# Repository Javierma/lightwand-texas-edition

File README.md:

# Lightwand Texas Edition v 2.0

Copyright (C) May 2018, Javier Martínez Arrieta

The LightWand Texas Edition controller is released under an Attributtion-ShareAlike 4.0 International (CC BY-SA 4.0). Therefore, anyone is free to:

-Share - copy and redistribute the material in any medium or format

-Adapt - remix, transform, and build upon the material for any purpose, even commercially.

This is the Lightwand Texas Edition project, a light painting project that makes use of a TM4C123 (TIVA) board as a controller in order to read the image information and transmit it to the LED strip according to the settings.

The following folders contain all the necessary things:
	
-CCS project: Contains the software code to be uploaded to the board

-Eagle project: Contains the hardware design

-FreeCAD design: Contains the 3D design of the box to cover the hardware

-Sketchup design: Contains the 3D design of the hardware

-Lightwand Texas Edition English Guide: The manual to be used to know about the different HW parts, soldering steps, creating PNM images and how to navigate through the different menus 

In order to know how to import the project in Code Composer Studio, configure the project settings and configure interrupts, go to the [wiki page](https://github.com/Javierma/lightwand-texas-edition/wiki)

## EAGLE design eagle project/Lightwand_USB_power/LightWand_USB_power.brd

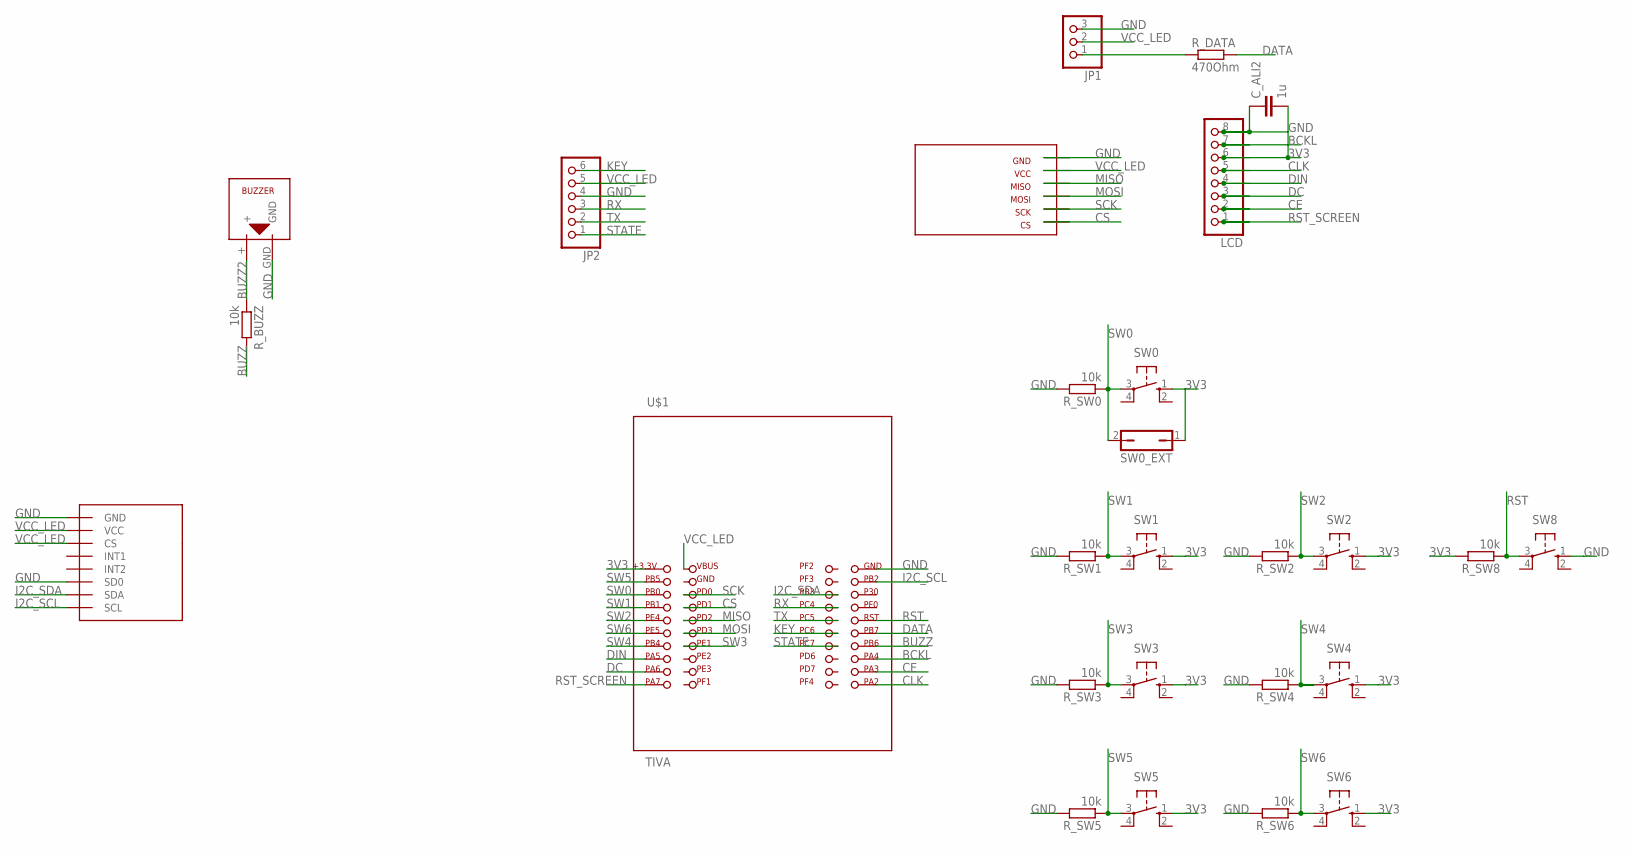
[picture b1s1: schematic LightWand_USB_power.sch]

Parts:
C_ALI2: 1u; C1206
JP1: PINHD-1X3; 1X03
JP2: PINHD-1X6; 1X06
LCD: PINHD-1X8; 1X08
R_BUZZ: 10k; R1206
R_DATA: 470Ohm; R1206
R_SW0, R_SW1, R_SW2, R_SW3, R_SW4, R_SW5, R_SW6, R_SW8: 10k; R1206
SW0, SW1, SW2, SW3, SW4, SW5, SW6, SW8: 10-XX; B3F-10XX
SW0_EXT: JP1Q; JP1
U$1: TIVA; TIVACSERIES
U$2: ADXL345
U$3: MURATA_BUZZER
U$4: SD_READER_CATALEX

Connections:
3V3: C_ALI2.2, LCD.6, R_SW8.2, SW0.1 (S), SW0_EXT.1, SW1.1 (S), SW2.1 (S), SW3.1 (S), SW4.1 (S), SW5.1 (S), SW6.1 (S), U$1.+3.3V (3.3V)
BCKL: LCD.7, U$1.PA4
BUZZ: R_BUZZ.2, U$1.PB6
BUZZ2: R_BUZZ.1, U$3.+
CE: LCD.2, U$1.PA3
CLK: LCD.5, U$1.PA2
CS: U$1.PD1, U$4.CS
DATA: R_DATA.2, U$1.PB7
DC: LCD.3, U$1.PA6
DIN: LCD.4, U$1.PA5
GND: C_ALI2.1, JP1.3, JP2.4, LCD.8, R_SW0.2, R_SW1.2, R_SW2.2, R_SW3.2, R_SW4.2, R_SW5.2, R_SW6.2, SW8.1 (S), U$1.GND1 (GND2), U$2.P$1 (GND), U$2.P$6 (SD0), U$3.GND, U$4.GND
I2C_SCL: U$1.PB2, U$2.P$7 (SCL)
I2C_SDA: U$1.PB3, U$2.P$8 (SDA)
KEY: JP2.6, U$1.PC6
MISO: U$1.PD2, U$4.MISO
MOSI: U$1.PD3, U$4.MOSI
unnamed: JP1.1, R_DATA.1
RST: R_SW8.1, SW8.3, U$1.RST
RST_SCREEN: LCD.1, U$1.PA7
RX: JP2.3, U$1.PC4
SCK: U$1.PD0, U$4.SCK
STATE: JP2.1, U$1.PC7
SW0: R_SW0.1, SW0.3, SW0_EXT.2, U$1.PB0
SW1: R_SW1.1, SW1.3, U$1.PB1
SW2: R_SW2.1, SW2.3, U$1.PE4
SW3: R_SW3.1, SW3.3, U$1.PE1
SW4: R_SW4.1, SW4.3, U$1.PB4
SW5: R_SW5.1, SW5.3, U$1.PB5
SW6: R_SW6.1, SW6.3, U$1.PE5
TX: JP2.2, U$1.PC5
VCC_LED: JP1.2, JP2.5, U$1.VBUS, U$2.P$2 (VCC), U$2.P$3 (CS), U$4.VCC

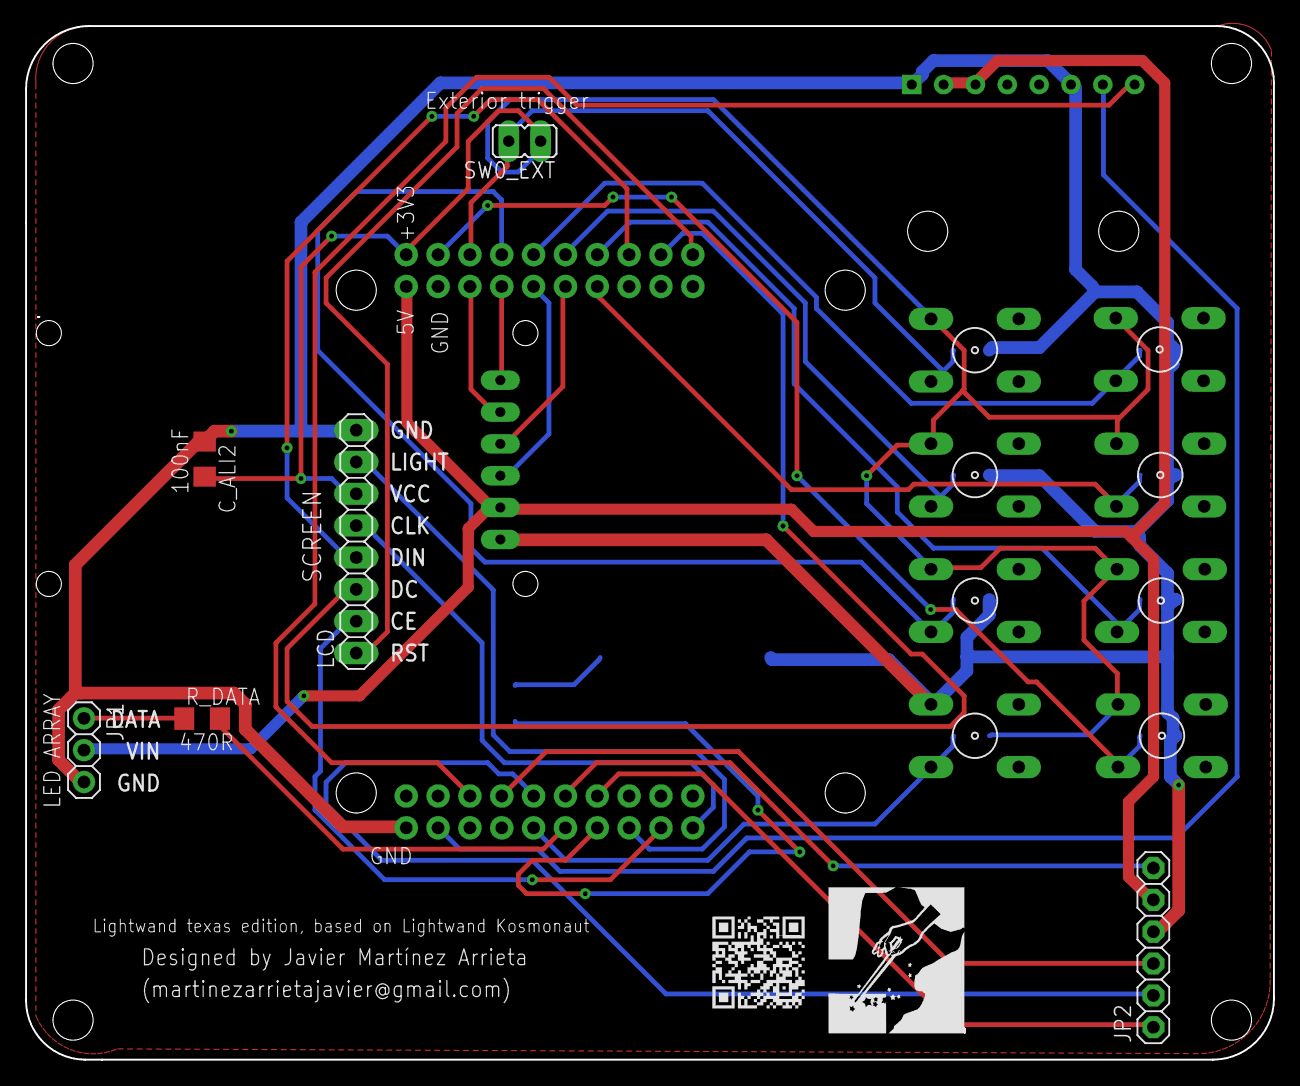
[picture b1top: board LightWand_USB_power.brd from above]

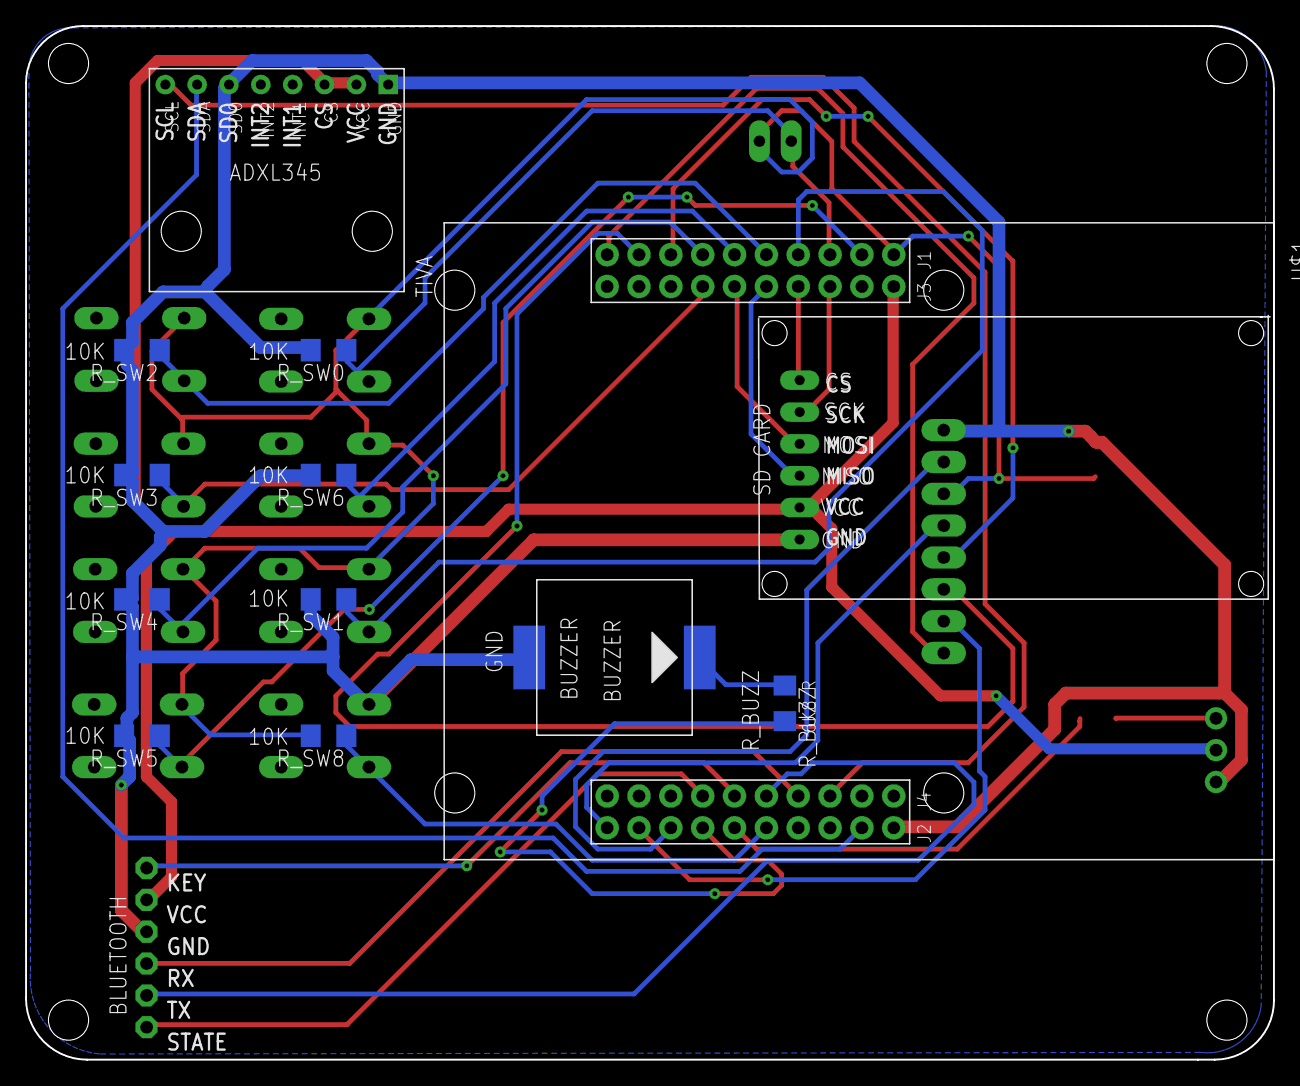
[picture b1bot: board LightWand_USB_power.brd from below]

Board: 2 copper layers, 99.5 x 82.4 mm, 27 parts (13 on the bottom side), 31 nets.

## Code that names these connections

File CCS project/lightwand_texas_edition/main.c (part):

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				{
					switch(portB_data)
					{
						case 0x01: //PB0 (Change backlight status)
						{

						break;
						}
						case 0x02: //PB1 (Select element at current position)
						{
							if(current_position==2)
							{
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				{
					switch(portE_data)
					{
						case 0x02: // PE1 (down)
						{
							if(current_position==2)
							{
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							}
							break;
						}
						case 0x20: // PE5 (up)
						{
							if(current_position==3)
							{
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    volatile unsigned long delay;
    SYSCTL_RCGC2_R |= 0x00000012;           //  activate clock for Ports B and E
    delay = SYSCTL_RCGC2_R;                 //  allow time for clock to stabilize
    GPIO_PORTB_DIR_R &= ~0x33;             // make PB0,1,4 and 5 in
    GPIO_PORTB_AFSEL_R &= ~0x33;           // disable alt funct on PA2,3,5
    GPIO_PORTB_DEN_R |= 0x33;             // enable digital I/O on PB0,1,4 and 5

    GPIO_PORTB_PCTL_R &= ~0x00FF00FF;    //Configure PB0, 1, 4 and 5 as GPIO
    GPIO_PORTB_AMSEL_R &= ~0x33;           // disable alt funct on PB0,1,4 and 5
    GPIO_PORTB_IS_R &= ~0x33;            //PB0,1,4 and 5 are edge sensitive
    GPIO_PORTB_IBE_R &= ~0x33;            //Disable both edges for PB0,1,4 and 5
    //GPIO_PORTB_IEV_R &= ~0x33;            //Detect falling edge in PB0,1,4 and 5
    GPIO_PORTB_IEV_R |= 0x33;            //Detect rising edge in PB0,1,4 and 5
    GPIO_PORTB_ICR_R = 0x33;              // ack, clear interrupt flags for PB0,1,4 and 5
    GPIO_PORTB_IM_R |= 0x33;              // arm interrupt on PB0,1,4 and 5
    NVIC_PRI0_R = (NVIC_PRI0_R&0xFFFF1FFF)|0x0000E000;         //Set priority bits for port B
    NVIC_EN0_R |= 0x00000002;      // (h) enable interrupt 1 in NVIC (seen in IRQ). Interrupt one is bit 1


    GPIO_PORTE_DIR_R &= ~0x32;             // make PE1,4 and 5 in
    GPIO_PORTE_AFSEL_R &= ~0x32;           // disable alt funct on PE1,4 and 5
    GPIO_PORTE_DEN_R |= 0x32;             // enable digital I/O on PE1,4 and 5


    GPIO_PORTE_PCTL_R &= ~0x00FF00F0;    //Configure PE1,4 and 5 as GPIO
    GPIO_PORTE_AMSEL_R &= ~0x32;           // disable alt funct on PE1, 4 and 5
    GPIO_PORTE_IS_R &= ~0x32;            //PE1, 4 and 5 are edge sensitive
    GPIO_PORTE_IBE_R &= ~0x32;            //Disable both edges for PE1, 4 and 5
    //GPIO_PORTE_IEV_R &= ~0x32;            //Detect falling edge in PE1, 4 and 5
    GPIO_PORTE_IEV_R |= 0x32;            //Detect rising edge in PE1, 4 and 5
    GPIO_PORTE_ICR_R = 0x32;              // ack, clear interrupt flags for PE1, 4 and 5
    GPIO_PORTE_IM_R |= 0x32;              // arm interrupt on PE1, PE4 and PE5
    NVIC_PRI1_R = (NVIC_PRI1_R&0xFFFFFF1F)|0x000000E0;         //Set priority bits for port E
    NVIC_EN0_R |= 0x00000010;      // (h) enable interrupt 1 in NVIC (seen in IRQ). Interrupt one is bit 4

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    int led_position=0;
    char c,c2,go_back=0,just_came=0;
    //Check which pin caused the interrupt
    //Backlight pin (PB0)
    if(GPIO_PORTB_RIS_R&0x01)
    {
        GPIO_PORTB_ICR_R |= 0x01; // ack, clear interrupt flag0
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    }
    else
    {
        //Minus/decrease pin (PB4)
        if(GPIO_PORTB_RIS_R&0x10)
        {
            GPIO_PORTB_ICR_R |= 0x10; // ack, clear interrupt flag4
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        }
        else
        {
            //Select pin (PB1)
            if(GPIO_PORTB_RIS_R&0x02)
            {
                GPIO_PORTB_ICR_R |= 0x02; // ack, clear interrupt flag1
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            }
            else
            {
                //Start pin (PB5)
                if(GPIO_PORTB_RIS_R&0x20)
                {
                    GPIO_PORTB_ICR_R |= 0x20; // ack, clear interrupt flag5
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    int led_position=0;
    char c,c2,go_back=0,just_came=0,lights=LIGHTS_OFF;
    //check which pin caused the interrupt
    //Move down pin (PE1)
    if(GPIO_PORTE_RIS_R&0x02)
    {
        GPIO_PORTE_ICR_R |= 0x02; // ack, clear interrupt flag1
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    }
    else
    {
        //More/Increase pin (PE4)
        if(GPIO_PORTE_RIS_R&0x10)
        {
            GPIO_PORTE_ICR_R |= 0x10; // ack, clear interrupt flag4
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        }
        else
        {
            //Move up pin (PE5)
            if(GPIO_PORTE_RIS_R&0x20)
            {
                GPIO_PORTE_ICR_R |= 0x20; // ack, clear interrupt flag5
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	//Port B has already been initialized, so clock does not have to be set again
	SYSCTL_RCGCI2C_R |=SYSCTL_RCGCI2C_R0; //Enable clock for the I2C module
	delay=SYSCTL_RCGCI2C_R;
	GPIO_PORTB_AFSEL_R |= 0x0C;           // disable alt funct on PB2 and 3
    // configure PB2 and 3 I2C
	GPIO_PORTB_PCTL_R = (GPIO_PORTB_PCTL_R&0xFFFF00FF)+0x00003300;
    // configure PA6,7 as GPIO
	GPIO_PORTB_PCTL_R = (GPIO_PORTB_PCTL_R&0xFF00FF0F)+0x00000000;
	GPIO_PORTB_DEN_R |= 0x0C;   // enable digital I/O on PB2 and 3
	GPIO_PORTB_ODR_R |=0x08;	// enable SDA for open drain operation
	I2C0_MCR_R |=I2C_MCR_MFE;	//Initialization of I2C master
	I2C0_MTPR_R |=0x00000007;	//Sets I2C clock speed to 100Kbps with 16MHz oscillator
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	SYSCTL_RCGCTIMER_R |= 0x01;      // activate timer0
	SYSCTL_RCGC2_R |= 0x00000002;   //  activate clock for Port B
	delay = SYSCTL_RCGC2_R;
	GPIO_PORTB_DIR_R |= 0x40;             // make PB6 out
	GPIO_PORTB_AFSEL_R |= 0x40;           // enable alt funct on PB6
	GPIO_PORTB_AMSEL_R &= ~0x40;          // disable analog functionality on PB6
	GPIO_PORTB_DEN_R |= 0x40;

	GPIO_PORTB_PCTL_R = (GPIO_PORTB_PCTL_R&0xF0FFFFFF)+0x07000000;
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
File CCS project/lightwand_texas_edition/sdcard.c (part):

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	delay = SYSCTL_RCGC2_R;         		// allow time for clock to stabilize
	GPIO_PORTD_LOCK_R=0x4C4F434B;
	GPIO_PORTD_CR_R=0x80;
	GPIO_PORTD_DIR_R |= 0x08;             // make PD3 out
	GPIO_PORTD_AFSEL_R |= 0x0D;           // enable alt funct on PD0, PD2 and PD3
	GPIO_PORTD_AFSEL_R &= ~0xF2;          // disable alt funct on PD1
	GPIO_PORTD_DEN_R |= 0x0F;             // enable digital I/O on PD0, PD1, PD2 and PD3
	// configure PD0, PD2 and PD3 as SSI
	GPIO_PORTD_PCTL_R = (GPIO_PORTD_PCTL_R&0xFFFF00F0)+0x00001101;
	// configure PD1 as GPIO
	GPIO_PORTD_PCTL_R = (GPIO_PORTD_PCTL_R&0xFFFFFFF0F)+0x00000000;
	                                        // configure PD0, PD1 and PD3 as SSI
	GPIO_PORTD_AMSEL_R &= ~0xCF;          // disable analog functionality on PD0, PD1, PD2, PD3, PD6 and PD7
	SSI3_CR1_R&=~SSI_CR1_SSE;		  		// Disable SSI while configuring it
	SSI3_CR1_R&=~SSI_CR1_MS;		  		// Set as Master
	SSI3_CC_R|=SSI_CC_CS_M; 				// Configure clock source
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 */
void tx_high()
{
	GPIO_PORTD_AFSEL_R &= ~0x08;           // disable alt funct on PD3
	GPIO_PORTD_PCTL_R = (GPIO_PORTD_PCTL_R&0xFFFF0FFF);
	GPIO_PORTD_DATA_R |= 0x08;            // PD3 high
}

/*
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 */
void tx_SSI()
{
	GPIO_PORTD_AFSEL_R |= 0x08;           // enable alt funct on PD3
	GPIO_PORTD_PCTL_R = (GPIO_PORTD_PCTL_R&0xFFFF0FFF)+0x00001000;
}

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
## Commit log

2018-04-30 Lightwand Texas Edition v1.0
2018-05-01 Added mobile camera setup
2018-05-01 Cleared code that appeared as comments
2018-05-01 Solved problem with buzzer sound
2018-05-01 README format update
2018-05-04 Added guide in Spanish
2018-05-27 Guides have been updated with box mount
2018-11-25 Added Bill of Materials
2020-07-25 Update to version 2.0. In this version the code was changed to interrupts
2020-11-02 Modified code to be able to read the name of the files set by the user

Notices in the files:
CCS project/lightwand_texas_edition/sdcard.c:
Copyright (C) 2016 Javier Martínez Arrieta
This project is licensed under Creative Commons Attribution-Non Commercial-Share Alike 4.0 International (CC BY-NC-SA 4.0). According to this license you are free to:
Complete information about this license can be found at: https://creativecommons.org/licenses/by-nc-sa/4.0/legalcode
Embedded Systems: Real-Time Operating Systems for ARM Cortex-M Microcontrollers, Volume 3,
ISBN: 978-1466468863, Jonathan Valvano, copyright (c) 2013
Copyright 2013 by Jonathan W. Valvano, valvano@mail.utexas.edu
